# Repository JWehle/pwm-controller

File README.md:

# pwm-controller
Custom PWM controller circuit for DCDC boards

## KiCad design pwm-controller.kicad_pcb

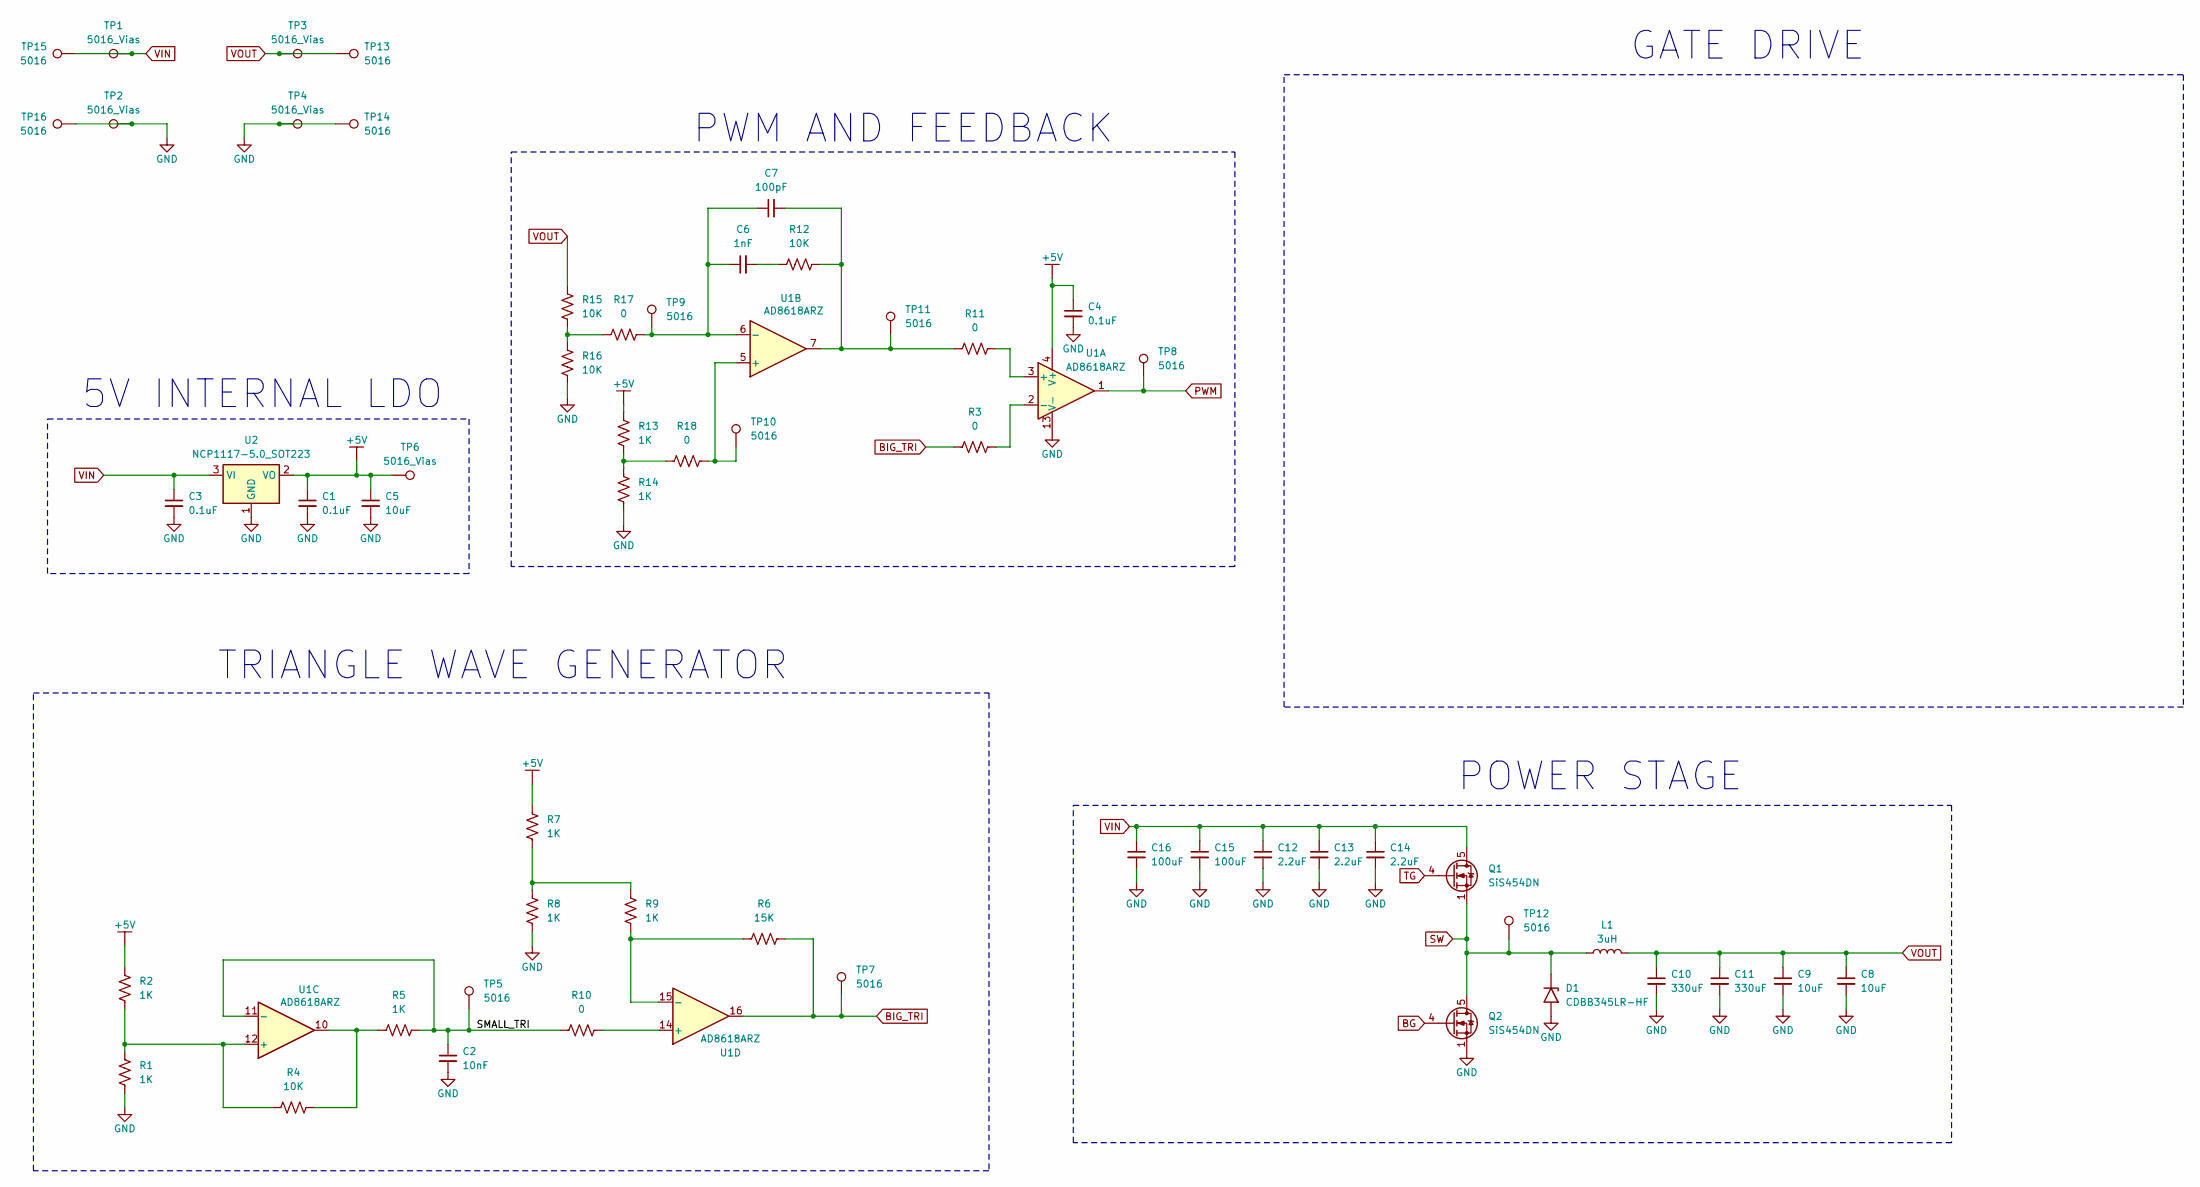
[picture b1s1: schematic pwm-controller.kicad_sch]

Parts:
C1, C3, C4: 0.1uF; C_0603_1608Metric_Pad1.08x0.95mm_HandSolder
C2: 10nF; C_0603_1608Metric_Pad1.08x0.95mm_HandSolder
C5, C8, C9: 10uF; C_1206_3216Metric_Pad1.33x1.80mm_HandSolder
C6: 1nF; C_0603_1608Metric_Pad1.08x0.95mm_HandSolder
C7: 100pF; C_0603_1608Metric_Pad1.08x0.95mm_HandSolder
C10, C11: 330uF; CP_EIA-7343-43_Kemet-X_Pad2.25x2.55mm_HandSolder
C12, C13, C14: 2.2uF; C_1206_3216Metric_Pad1.33x1.80mm_HandSolder
C15, C16: 100uF; CP_Elec_6.3x5.4_Nichicon
D1: CDBB345LR-HF; D_SMB
L1: 3uH; L_Coilcraft_MSS1260-XXX
Q1, Q2: SiS454DN; Vishay_PowerPAK_1212-8_Single
R1, R2, R5, R7, R8, R9, R13, R14: 1K; R_0603_1608Metric_Pad0.98x0.95mm_HandSolder
R3, R10, R11, R17, R18: 0; R_0603_1608Metric_Pad0.98x0.95mm_HandSolder
R4, R12, R15, R16: 10K; R_0603_1608Metric_Pad0.98x0.95mm_HandSolder
R6: 15K; R_0603_1608Metric_Pad0.98x0.95mm_HandSolder
TP1, TP2, TP3, TP4, TP6: 5016_Vias; TestPoint_Keystone_5016_Vias
TP5, TP7, TP8, TP9, TP10, TP11, TP12, TP13, TP14, TP15, TP16: 5016; TestPoint_Keystone_5016_Compact
U1: AD8618ARZ; SOIC-16_3.9x9.9mm_P1.27mm
U2: NCP1117-5.0_SOT223; SOT-223-3_TabPin2

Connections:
+5V: C1.1, C4.1, C5.1, R2.1, R7.1, R13.1, TP6.1, U1.4 (V+), U2.2 (VO)
/SMALL_TRI: C2.1, R5.2, R10.1, TP5.1, U1.11 (-)
BG: Q2.4 (G)
BIG_TRI: R3.1, R6.2, TP7.1, U1.16
GND: C1.2, C2.2, C3.2, C4.2, C5.2, C8.2, C9.2, C10.2, C11.2, C12.2, C13.2, C14.2, C15.2, C16.2, D1.2 (A2), Q2.1 (S), Q2.2 (S), Q2.3 (S), R1.2, R8.2, R14.2, R16.2, TP2.1, TP4.1, TP14.1, TP16.1, U1.13 (V-), U2.1 (GND)
unnamed: C6.2, R12.1
unnamed: C7.2, R11.1, R12.2, TP11.1, U1.7
unnamed: R4.2, R5.1, U1.10
unnamed: R7.2, R8.1, R9.1
unnamed: R13.2, R14.1, R18.1
unnamed: R15.2, R16.1, R17.1
unnamed: R11.2, U1.3 (+)
unnamed: R3.2, U1.2 (-)
unnamed: R18.2, TP10.1, U1.5 (+)
unnamed: C6.1, C7.1, R17.2, TP9.1, U1.6 (-)
unnamed: R1.1, R2.2, R4.1, U1.12 (+)
unnamed: R10.2, U1.14 (+)
unnamed: R6.1, R9.2, U1.15 (-)
PWM: TP8.1, U1.1
SW: D1.1 (A1), L1.1, Q1.1 (S), Q1.2 (S), Q1.3 (S), Q2.5 (D), TP12.1
TG: Q1.4 (G)
VIN: C3.1, C12.1, C13.1, C14.1, C15.1, C16.1, Q1.5 (D), TP1.1, TP15.1, U2.3 (VI)
VOUT: C8.1, C9.1, C10.1, C11.1, L1.2, R15.1, TP3.1, TP13.1

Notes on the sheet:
PWM AND FEEDBACK
POWER STAGE
GATE DRIVE
5V INTERNAL LDO
TRIANGLE WAVE GENERATOR

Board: 2 copper layers, 56 parts (0 on the bottom side), 21 nets, no tracks yet.

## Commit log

2025-12-04 some schematic work
    some of schematic is complete
2025-12-04 schematic edits
    some schematic edits
2025-12-04 schematic images
    and placement
